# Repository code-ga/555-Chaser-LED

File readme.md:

# 555 Chaser LED

This is the one led board with 5 effects. These effects are:

- Blinky effect (each led will light-up then off for next led)
- Bit Counting (That is the calculator with led)
- Bar led ( These Stack up each clock )
- Breath effect ( fade up and fade down )
- On Mode ( their light up all led their have )

This is the result board

Also for someone want to know how that work

Also with the BOM (bill of material) of project is

| Reference                                                                                               | Qty | Value             | Footprint                                                     | Datasheet                                                                       | LCSC Part # | DIGIKEY_LINK                                                             | Price |
|---------------------------------------------------------------------------------------------------------|-----|-------------------|---------------------------------------------------------------|---------------------------------------------------------------------------------|-------------|--------------------------------------------------------------------------|-------|
| C1                                                                                                      | 1   | 0.01uF            | Capacitor_THT:C_Disc_D7.5mm_W2.5mm_P5.00mm                    |                                                                                 | C52205045   |                                                                          | 0.56  |
| C2                                                                                                      | 1   | 33uF              | Capacitor_THT:CP_Radial_D5.0mm_P2.00mm                        |                                                                                 | C20539524   |                                                                          | 0.74  |
| D1,D2,D3,D4,D5,D6,D7,D8,D9,D10                                                                          | 10  | LED               | LED_THT:LED_D3.0mm                                            |                                                                                 | C99772      |                                                                          | 0.73  |
| D11,D12,D13,D14,D15,D16,D17,D18,D19,D20,D21,D22,D23,D24,D25,D26,D27,D28,D29,D30,D35,D36,D37,D38,D39,D40 | 26  | D                 | Diode_THT:D_DO-35_SOD27_P7.62mm_Horizontal                    |                                                                                 | C402212     |                                                                          | 0.47  |
| J1                                                                                                      | 1   |                   | Connector_PinSocket_2.54mm:PinSocket_1x02_P2.54mm_Vertical    |                                                                                 | C7499322    |                                                                          | 0.46  |
| J2                                                                                                      | 1   | Conn_01x01_Socket | Connector_PinSocket_2.54mm:PinSocket_1x01_P2.54mm_Vertical    |                                                                                 | C6302252    |                                                                          | 1.15  |
| Q1,Q2,Q3,Q4,Q5                                                                                          | 5   | NPN               | Package_TO_SOT_THT:TO-92_Inline                               | https://ngspice.sourceforge.io/docs/ngspice-html-manual/manual.xhtml#cha_BJTs   | C22751480   |                                                                          | 0.75  |
| R1,R3,R4,R16,R17                                                                                        | 5   | 1k                | Resistor_THT:R_Axial_DIN0207_L6.3mm_D2.5mm_P7.62mm_Horizontal |                                                                                 | C3359542    |                                                                          | 1.14  |
| R2,R5,R6,R7,R8,R9,R10,R11,R12,R13,R14,R15                                                               | 12  | 470               | Resistor_THT:R_Axial_DIN0207_L6.3mm_D2.5mm_P7.62mm_Horizontal |                                                                                 | C1754684    |                                                                          | 2.74  |
| RV1                                                                                                     | 1   | 50k               | Potentiometer_THT:Potentiometer_Vishay_T93YA_Vertical         |                                                                                 | C7061697    |                                                                          | 3.2   |
| SW2                                                                                                     | 1   | SW_Push           | Button_Switch_THT:SW_PUSH_6mm_H9.5mm                          |                                                                                 | C2689645    | https://www.digikey.com/en/products/detail/c-k/PVA1-OA-H1-1-2N-V2/417717 | 3.04  |
| U1                                                                                                      | 1   | NE555P            | Package_DIP:DIP-8_W7.62mm                                     | http://www.ti.com/lit/ds/symlink/ne555.pdf                                      | C46749      |                                                                          | 1.36  |
| U2,U6                                                                                                   | 2   | 4017              | CD4017BE:N16                                                  | http://www.intersil.com/content/dam/Intersil/documents/cd40/cd4017bms-22bms.pdf | C32710674   |                                                                          | 0.70  |
| U3,U5                                                                                                   | 2   | 74HC595           | 74HC595N:DIP16-2.54-20.32X5.84MM                              | http://www.ti.com/lit/ds/symlink/sn74hc595.pdf                                  | C78711      |                                                                          | 2.56  |
| U7                                                                                                      | 1   | CD74HC93E         | 74HC93:N14                                                    | https://www.ti.com/lit/gpn/cd74hc93                                             | C20345323   |                                                                          | 2.29  |

[lcsc bom price](./assets/export_project_20260619_130623.xls)

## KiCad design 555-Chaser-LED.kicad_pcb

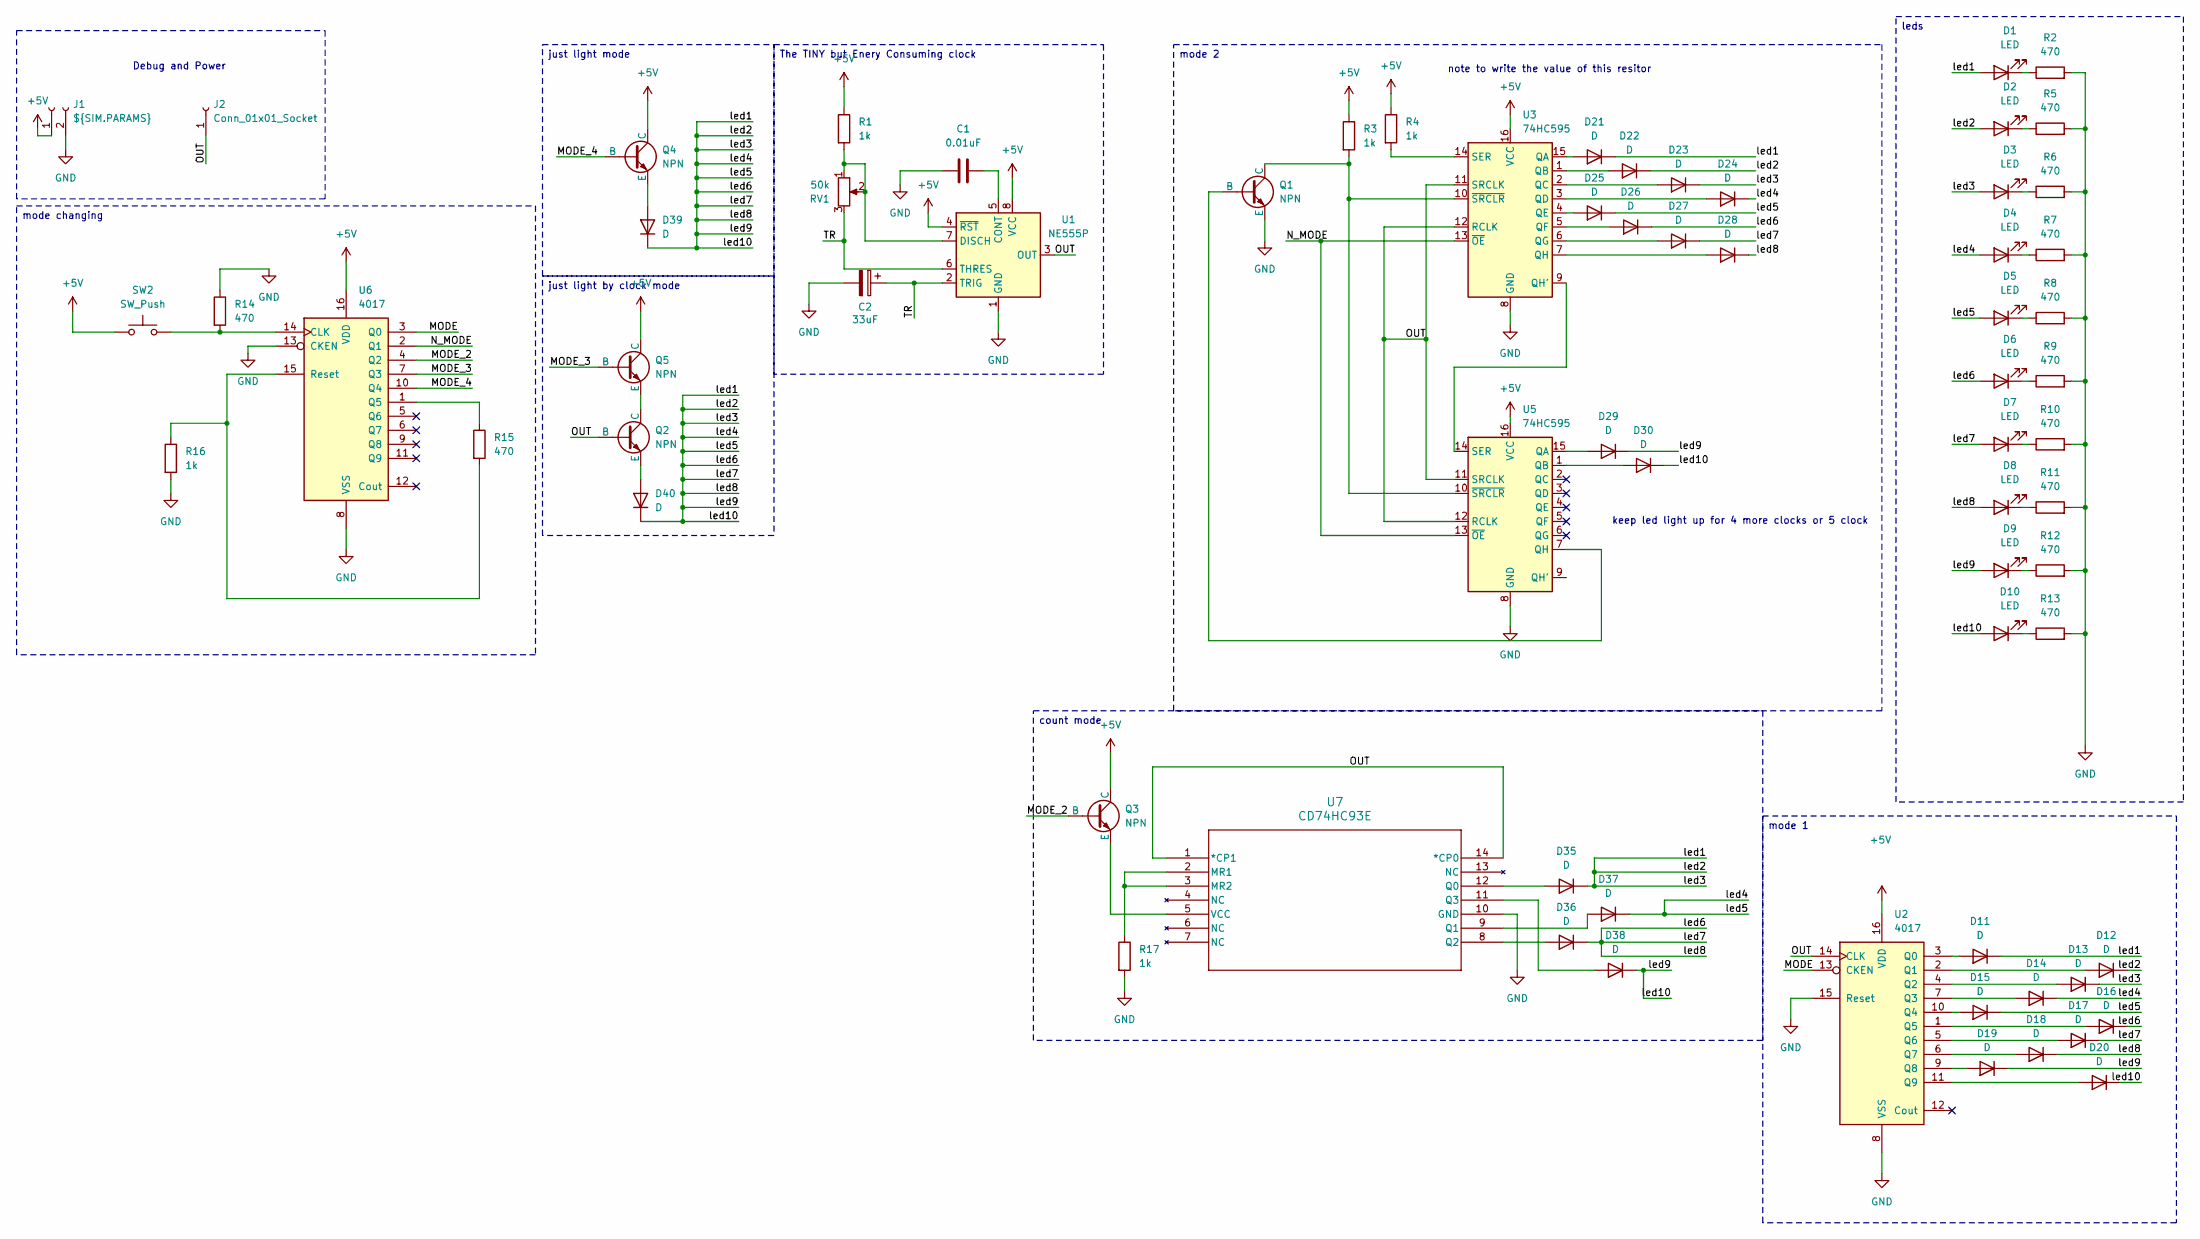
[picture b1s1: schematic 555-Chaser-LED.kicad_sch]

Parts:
C1: 0.01uF; C_Disc_D7.5mm_W2.5mm_P5.00mm
C2: 33uF; CP_Radial_D5.0mm_P2.00mm
D1, D2, D3, D4, D5, D6, D7, D8, D9, D10: LED; LED_D3.0mm
D11, D12, D13, D14, D15, D16, D17, D18, D19, D20, D21, D22, D23, D24, D25, D26, D27, D28, D29, D30, D35, D36, D37, D38, D39, D40: D; D_DO-35_SOD27_P7.62mm_Horizontal
J1: ${SIM.PARAMS}; PinSocket_1x02_P2.54mm_Vertical
J2: Conn_01x01_Socket; PinSocket_1x01_P2.54mm_Vertical
Q1, Q2, Q3, Q4, Q5: NPN; TO-92_Inline
R1, R3, R4, R16, R17: 1k; R_Axial_DIN0207_L6.3mm_D2.5mm_P7.62mm_Horizontal
R2, R5, R6, R7, R8, R9, R10, R11, R12, R13, R14, R15: 470; R_Axial_DIN0207_L6.3mm_D2.5mm_P7.62mm_Horizontal
RV1: 50k; Potentiometer_Vishay_T93YA_Vertical
SW2: SW_Push; SW_PUSH_6mm_H9.5mm
U1: NE555P; DIP-8_W7.62mm
U2, U6: 4017; N16
U3, U5: 74HC595; DIP16-2.54-20.32X5.84MM
U7: CD74HC93E; N14

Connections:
+5V: J1.1, Q3.1 (C), Q4.1 (C), Q5.1 (C), R1.1, R3.1, R4.1, SW2.1, U1.4 (~RST), U1.8 (VCC), U2.16 (VDD), U3.16 (VCC), U5.16 (VCC), U6.16 (VDD)
/MODE: U2.13 (CKEN), U6.3 (Q0)
/MODE_2: Q3.2 (B), U6.4 (Q2)
/MODE_3: Q5.2 (B), U6.7 (Q3)
/MODE_4: Q4.2 (B), U6.10 (Q4)
/N_MODE: U3.13 (~OE), U5.13 (~OE), U6.2 (Q1)
/OUT: J2.1 (Pin_1_1), Q2.2 (B), U1.3 (OUT), U2.14 (CLK), U3.11 (SRCLK), U3.12 (RCLK), U5.11 (SRCLK), U5.12 (RCLK), U7.1 (*CP1), U7.14 (*CP0)
/TR: C2.1, RV1.3, U1.2 (TRIG), U1.6 (THRES)
/led1: D1.2 (A), D2.2 (A), D3.2 (A), D4.2 (A), D5.2 (A), D6.2 (A), D7.2 (A), D8.2 (A), D9.2 (A), D10.2 (A), D11.1 (K), D12.1 (K), D13.1 (K), D14.1 (K), D15.1 (K), D16.1 (K), D17.1 (K), D18.1 (K), D19.1 (K), D20.1 (K), D21.1 (K), D22.1 (K), D23.1 (K), D24.1 (K), D25.1 (K), D26.1 (K), D27.1 (K), D28.1 (K), D29.1 (K), D30.1 (K), D35.1 (K), D36.1 (K), D37.1 (K), D38.1 (K), D39.1 (K), D40.1 (K)
GND: C1.1, C2.2, J1.2, Q1.3 (E), R2.2, R5.2, R6.2, R7.2, R8.2, R9.2, R10.2, R11.2, R12.2, R13.2, R14.1, R16.2, R17.2, U1.1 (GND), U2.8 (VSS), U2.15 (Reset), U3.8 (GND), U5.8 (GND), U6.8 (VSS), U6.13 (CKEN), U7.10 (GND)
unnamed: D1.1 (K), R2.1
unnamed: D2.1 (K), R5.1
unnamed: D3.1 (K), R6.1
unnamed: D4.1 (K), R7.1
unnamed: D5.1 (K), R8.1
unnamed: D6.1 (K), R9.1
unnamed: D7.1 (K), R10.1
unnamed: D8.1 (K), R11.1
unnamed: D9.1 (K), R12.1
unnamed: D10.1 (K), R13.1
unnamed: D11.2 (A), U2.3 (Q0)
unnamed: D12.2 (A), U2.2 (Q1)
unnamed: D13.2 (A), U2.4 (Q2)
unnamed: D14.2 (A), U2.7 (Q3)
unnamed: D15.2 (A), U2.10 (Q4)
unnamed: D16.2 (A), U2.1 (Q5)
unnamed: D17.2 (A), U2.5 (Q6)
unnamed: D18.2 (A), U2.6 (Q7)
unnamed: D19.2 (A), U2.9 (Q8)
unnamed: D20.2 (A), U2.11 (Q9)
unnamed: D21.2 (A), U3.15 (QA)
unnamed: D22.2 (A), U3.1 (QB)
unnamed: D23.2 (A), U3.2 (QC)
unnamed: D24.2 (A), U3.3 (QD)
unnamed: D25.2 (A), U3.4 (QE)
unnamed: D26.2 (A), U3.5 (QF)
unnamed: D27.2 (A), U3.6 (QG)
unnamed: D28.2 (A), U3.7 (QH)
unnamed: D29.2 (A), U5.15 (QA)
unnamed: D30.2 (A), U5.1 (QB)
unnamed: D35.2 (A), U7.12 (Q0)
unnamed: D36.2 (A), U7.8 (Q2)
unnamed: D37.2 (A), U7.9 (Q1)
unnamed: D38.2 (A), U7.11 (Q3)
unnamed: D39.2 (A), Q4.3 (E)
unnamed: D40.2 (A), Q2.3 (E)
unnamed: Q1.2 (B), U5.7 (QH)
unnamed: Q1.1 (C), R3.2, U3.10 (~SRCLR), U5.10 (~SRCLR)
unnamed: Q2.1 (C), Q5.3 (E)
unnamed: Q3.3 (E), U7.5 (VCC)
unnamed: C1.2, U1.5 (CONT)
unnamed: R1.2, RV1.1, RV1.2, U1.7 (DISCH)
unnamed: U3.9 (QH'), U5.14 (SER)
unnamed: R4.2, U3.14 (SER)
unnamed: R14.2, SW2.2, U6.14 (CLK)
unnamed: R15.1, U6.1 (Q5)
unnamed: R15.2, R16.1, U6.15 (Reset)
unnamed: R17.1, U7.2 (MR1), U7.3 (MR2)

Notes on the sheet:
keep led light up for 4 more clocks or 5 clock
note to write the value of this resitor
Debug and Power
mode changing
just light mode
mode 1
The TINY but Enery Consuming clock
just light by clock mode
count mode
mode 2
leds

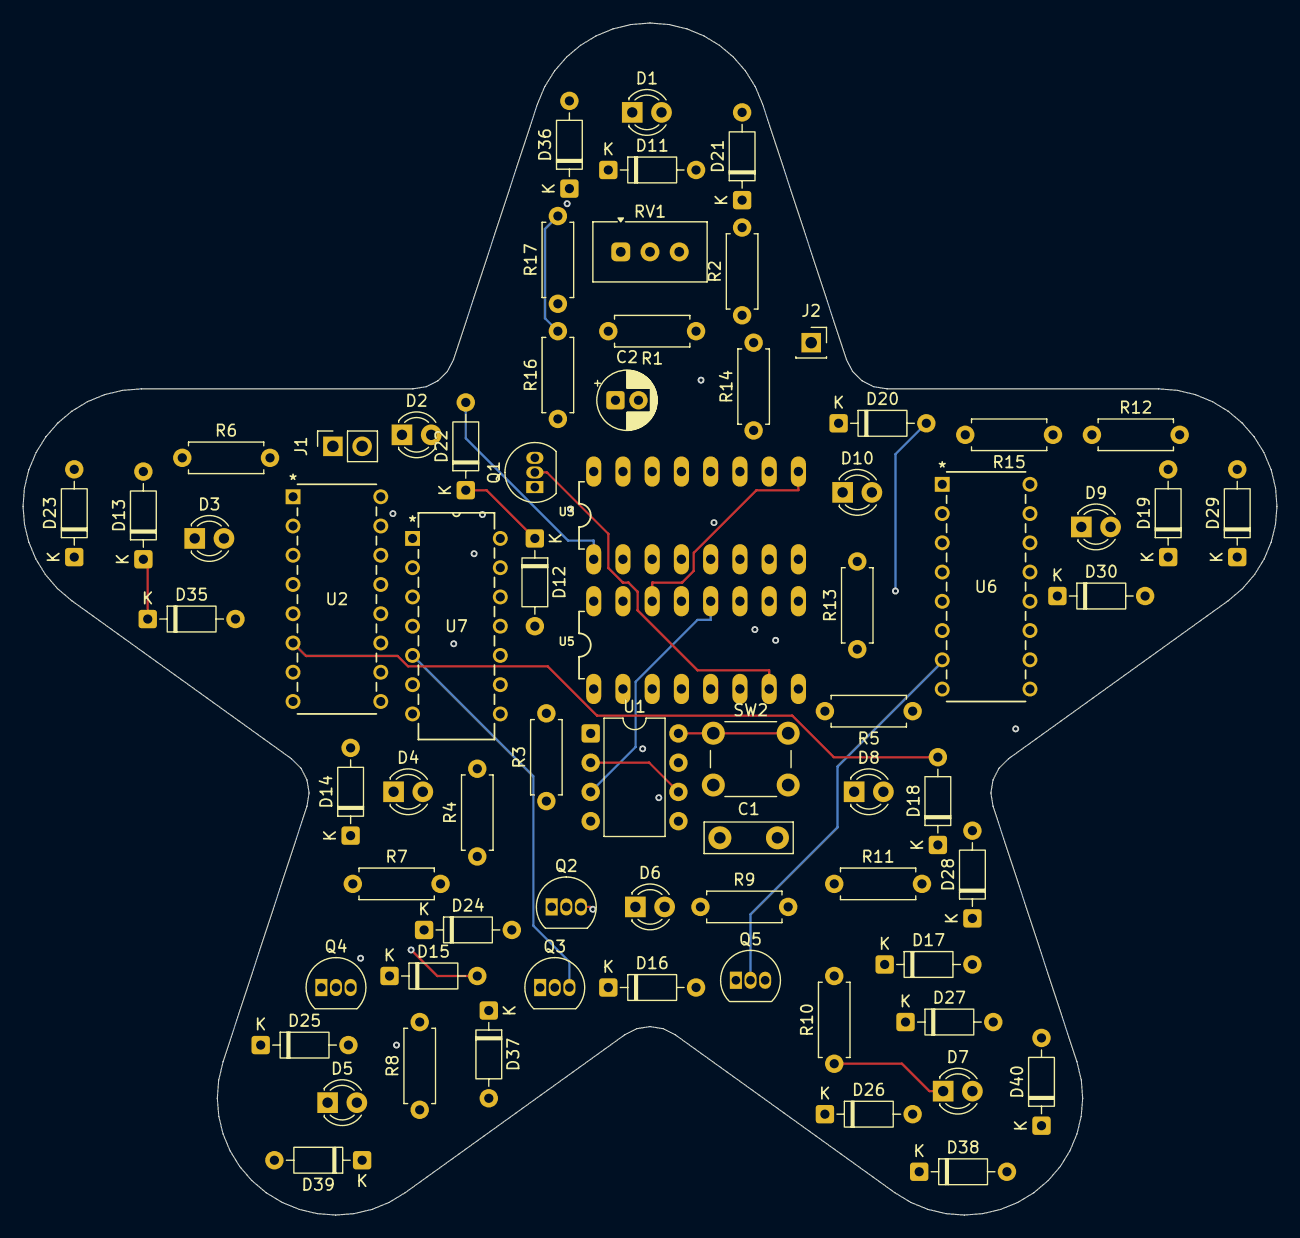
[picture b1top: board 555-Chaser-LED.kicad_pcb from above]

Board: 4 copper layers, 108.9 x 103.5 mm, 70 parts (0 on the bottom side), 58 nets.

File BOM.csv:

"Reference","Qty","Value","DNP","Exclude from BOM","Exclude from Board","Footprint","Datasheet","LCSC Part #","DIGIKEY_LINK","Price"
"C1","1","0.01uF",,,,"Capacitor_THT:C_Disc_D7.5mm_W2.5mm_P5.00mm",,"C52205045",,"0.56"
"C2","1","33uF",,,,"Capacitor_THT:CP_Radial_D5.0mm_P2.00mm",,"C20539524",,"0.74"
"D1,D2,D3,D4,D5,D6,D7,D8,D9,D10","10","LED",,,,"LED_THT:LED_D3.0mm",,"C99772",,"0.73"
"D11,D12,D13,D14,D15,D16,D17,D18,D19,D20,D21,D22,D23,D24,D25,D26,D27,D28,D29,D30,D35,D36,D37,D38,D39,D40","26","D",,,,"Diode_THT:D_DO-35_SOD27_P7.62mm_Horizontal",,"C402212",,"0.47"
"J1","1",,,,,"Connector_PinSocket_2.54mm:PinSocket_1x02_P2.54mm_Vertical",,C7499322,,0.46
"J2","1","Conn_01x01_Socket",,,,"Connector_PinSocket_2.54mm:PinSocket_1x01_P2.54mm_Vertical",,C6302252,,1.15
"Q1,Q2,Q3,Q4,Q5","5","NPN",,,,"Package_TO_SOT_THT:TO-92_Inline","https://ngspice.sourceforge.io/docs/ngspice-html-manual/manu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","C22751480",,0.75
"R1,R3,R4,R16,R17","5","1k",,,,"Resistor_THT:R_Axial_DIN0207_L6.3mm_D2.5mm_P7.62mm_Horizontal",,"C3359542",,"1.14"
"R2,R5,R6,R7,R8,R9,R10,R11,R12,R13,R14,R15","12","470",,,,"Resistor_THT:R_Axial_DIN0207_L6.3mm_D2.5mm_P7.62mm_Horizontal",,"C1754684",,"2.74"
"RV1","1","50k",,,,"Potentiometer_THT:Potentiometer_Vishay_T93YA_Vertical",,"C7061697",,"3.2"
"SW2","1","SW_Push",,,,"Button_Switch_THT:SW_PUSH_6mm_H9.5mm",,C2689645,https://www.digikey.com/en/products/detail/c-k/PVA1-OA-H1-1-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,3.04
"U1","1","NE555P",,,,"Package_DIP:DIP-8_W7.62mm","http://www.ti.com/lit/ds/symlink/ne555.pdf","C46749",,"1.36"
"U2,U6","2","4017",,,,"CD4017BE:N16","http://www.intersil.com/content/dam/Intersil/documents/cd40/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","C32710674",,0.70
"U3,U5","2","74HC595",,,,"74HC595N:DIP16-2.54-20.32X5.84MM","http://www.ti.com/lit/ds/symlink/sn74hc595.pdf",C78711,,2.56
"U7","1","CD74HC93E",,,,"74HC93:N14","https://www.ti.com/lit/gpn/cd74hc93",C20345323,,2.29

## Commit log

2026-06-19 init commit
2026-06-19 adding bom.csv
2026-06-19 add some image
